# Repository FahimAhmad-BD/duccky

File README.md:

# Duccky v1.0

A production intent digital twin of a 28 cm, 15 DOF bipedal duck robot: parametric CAD, wiring, URDF and MJCF, reinforcement learning policies, and the robot runtime, all generated from one master design and built with free tools only.

Inspired by Pollen Robotics' Microduck. Duccky is a clean sheet design and contains no Microduck mechanical files.

## Status

| Phase | Scope | Status |
|---|---|---|
| 0 | Requirements, DOF, mass and power budgets | Done, [DCK-00](docs/00_requirements.md) |
| 1 | Sim first actuator sizing and servo selection | Done, [DCK-01](docs/01_actuator_sizing.md) |
| 2 | Electrical architecture, KiCad carrier board, harness | Done, [DCK-02](docs/02_electrical.md) |
| 3 | Mechanical CAD in Fusion with DFM rules | Next |
| 4 | Engineering validation: FEA, tolerance stacks, range of motion, power | Planned |
| 5 | Robot description: URDF, MJCF, ROS 2 package | Planned |
| 6 | RL training and sim to sim transfer | Planned |
| 7 | Software in the loop runtime | Planned |
| 8 | Manufacturing package: BOM, drawings, print and assembly guides | Planned |
| 9 | Portfolio site with browser simulation | Planned |

## Key decisions so far

| Decision | Choice |
|---|---|
| Actuation | 6 × ROBOTIS XC330-M288-T (hip pitch, knee, ankle), 9 × XL330-M288-T, knee assist spring 0.10 N m/rad |
| Mass | 825 g against an 850 g limit |
| Compute | Radxa ZERO 3W, 4 GB, 16 GB eMMC |
| Battery | Tool-free 2S cartridge, 2 × Molicel INR-18650-P28A, 20.6 Wh |
| Height | about 29.7 cm in nominal stance |
| Leg | 5 DOF, no ankle roll, thigh 52 mm, shank 46 mm |

## Repository layout

```
cad/          Fusion API scripts, STEP, STL, drawings
ecad/         KiCad project, BOM, harness definition
description/  generated URDF, MJCF, ROS 2 package
analysis/     sizing, FEA, tolerance stacks, power budget
training/     RL environments, configs, ONNX policies
runtime/      robot software, hardware abstraction layer, sim drivers
docs/         design record
web/          browser demo
```

## Toolchain

Fusion (personal use) · FreeCAD FEM and TechDraw · KiCad · MuJoCo · Blender · Python · GitHub Pages. All free.

## License

Code: Apache 2.0. Design files and documentation: CC BY 4.0. Third party assets keep their own licenses, listed in [docs/asset_register.md](docs/asset_register.md).

Author: Fahim Ahmad

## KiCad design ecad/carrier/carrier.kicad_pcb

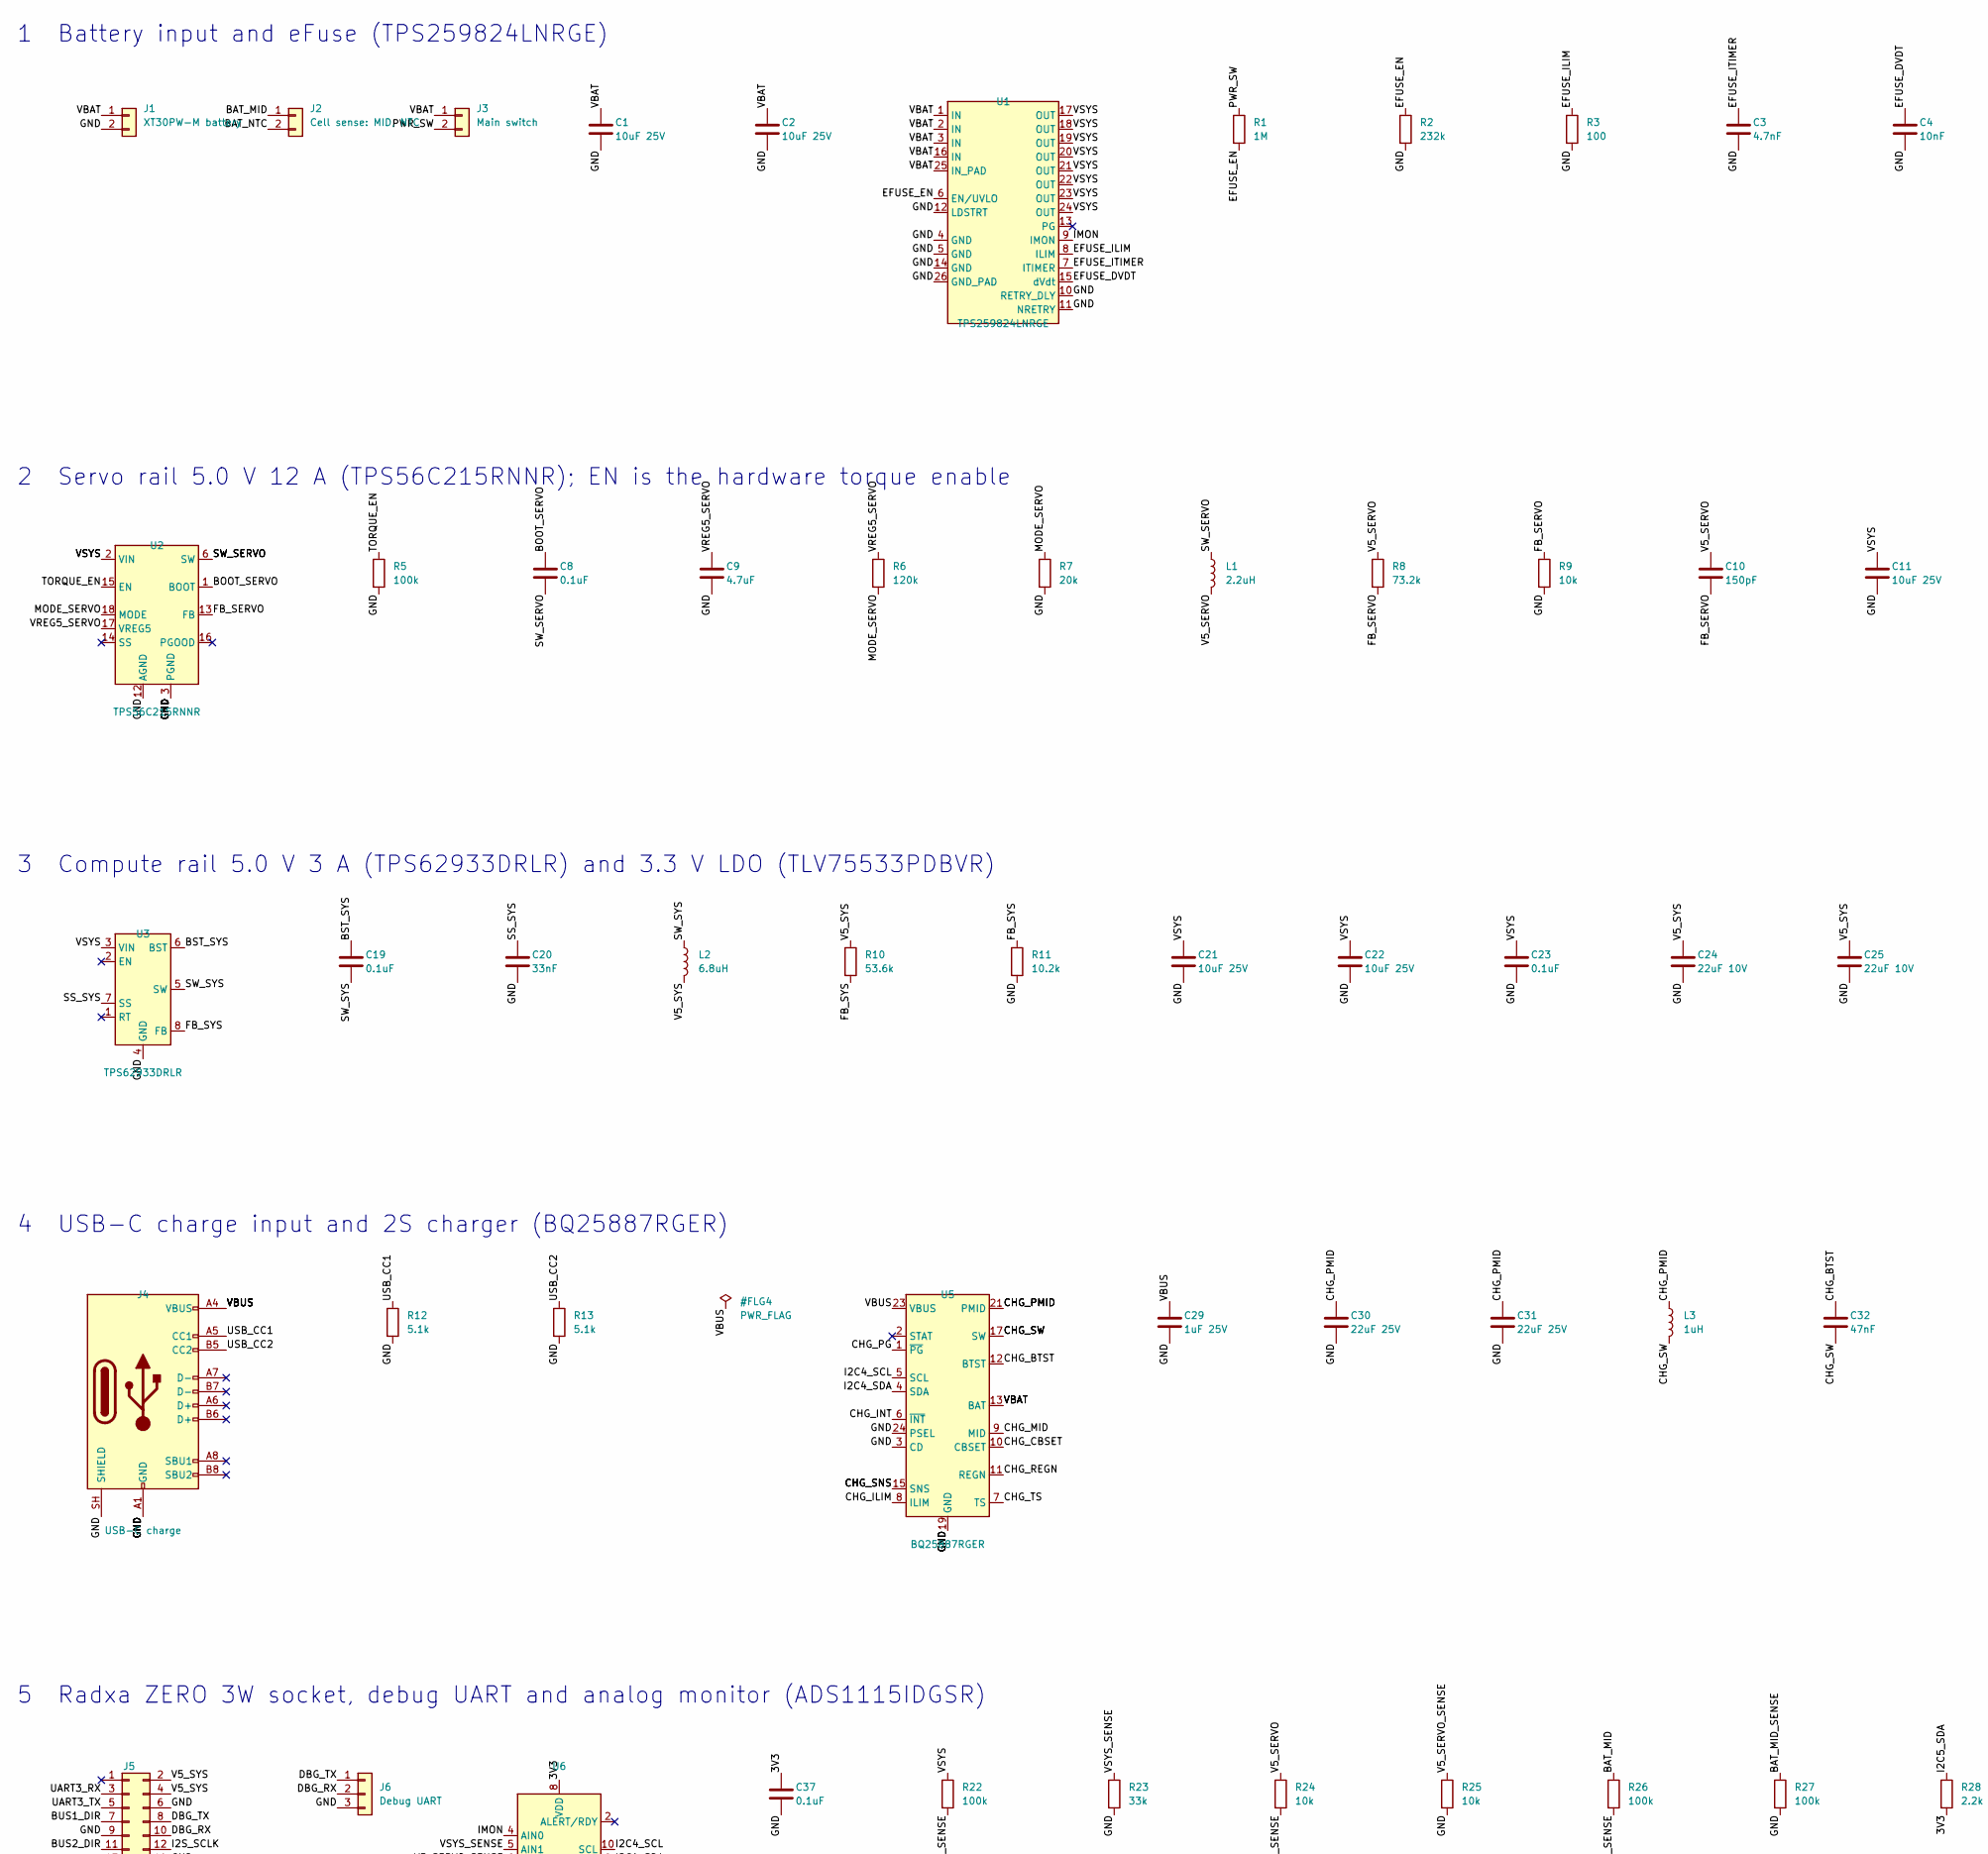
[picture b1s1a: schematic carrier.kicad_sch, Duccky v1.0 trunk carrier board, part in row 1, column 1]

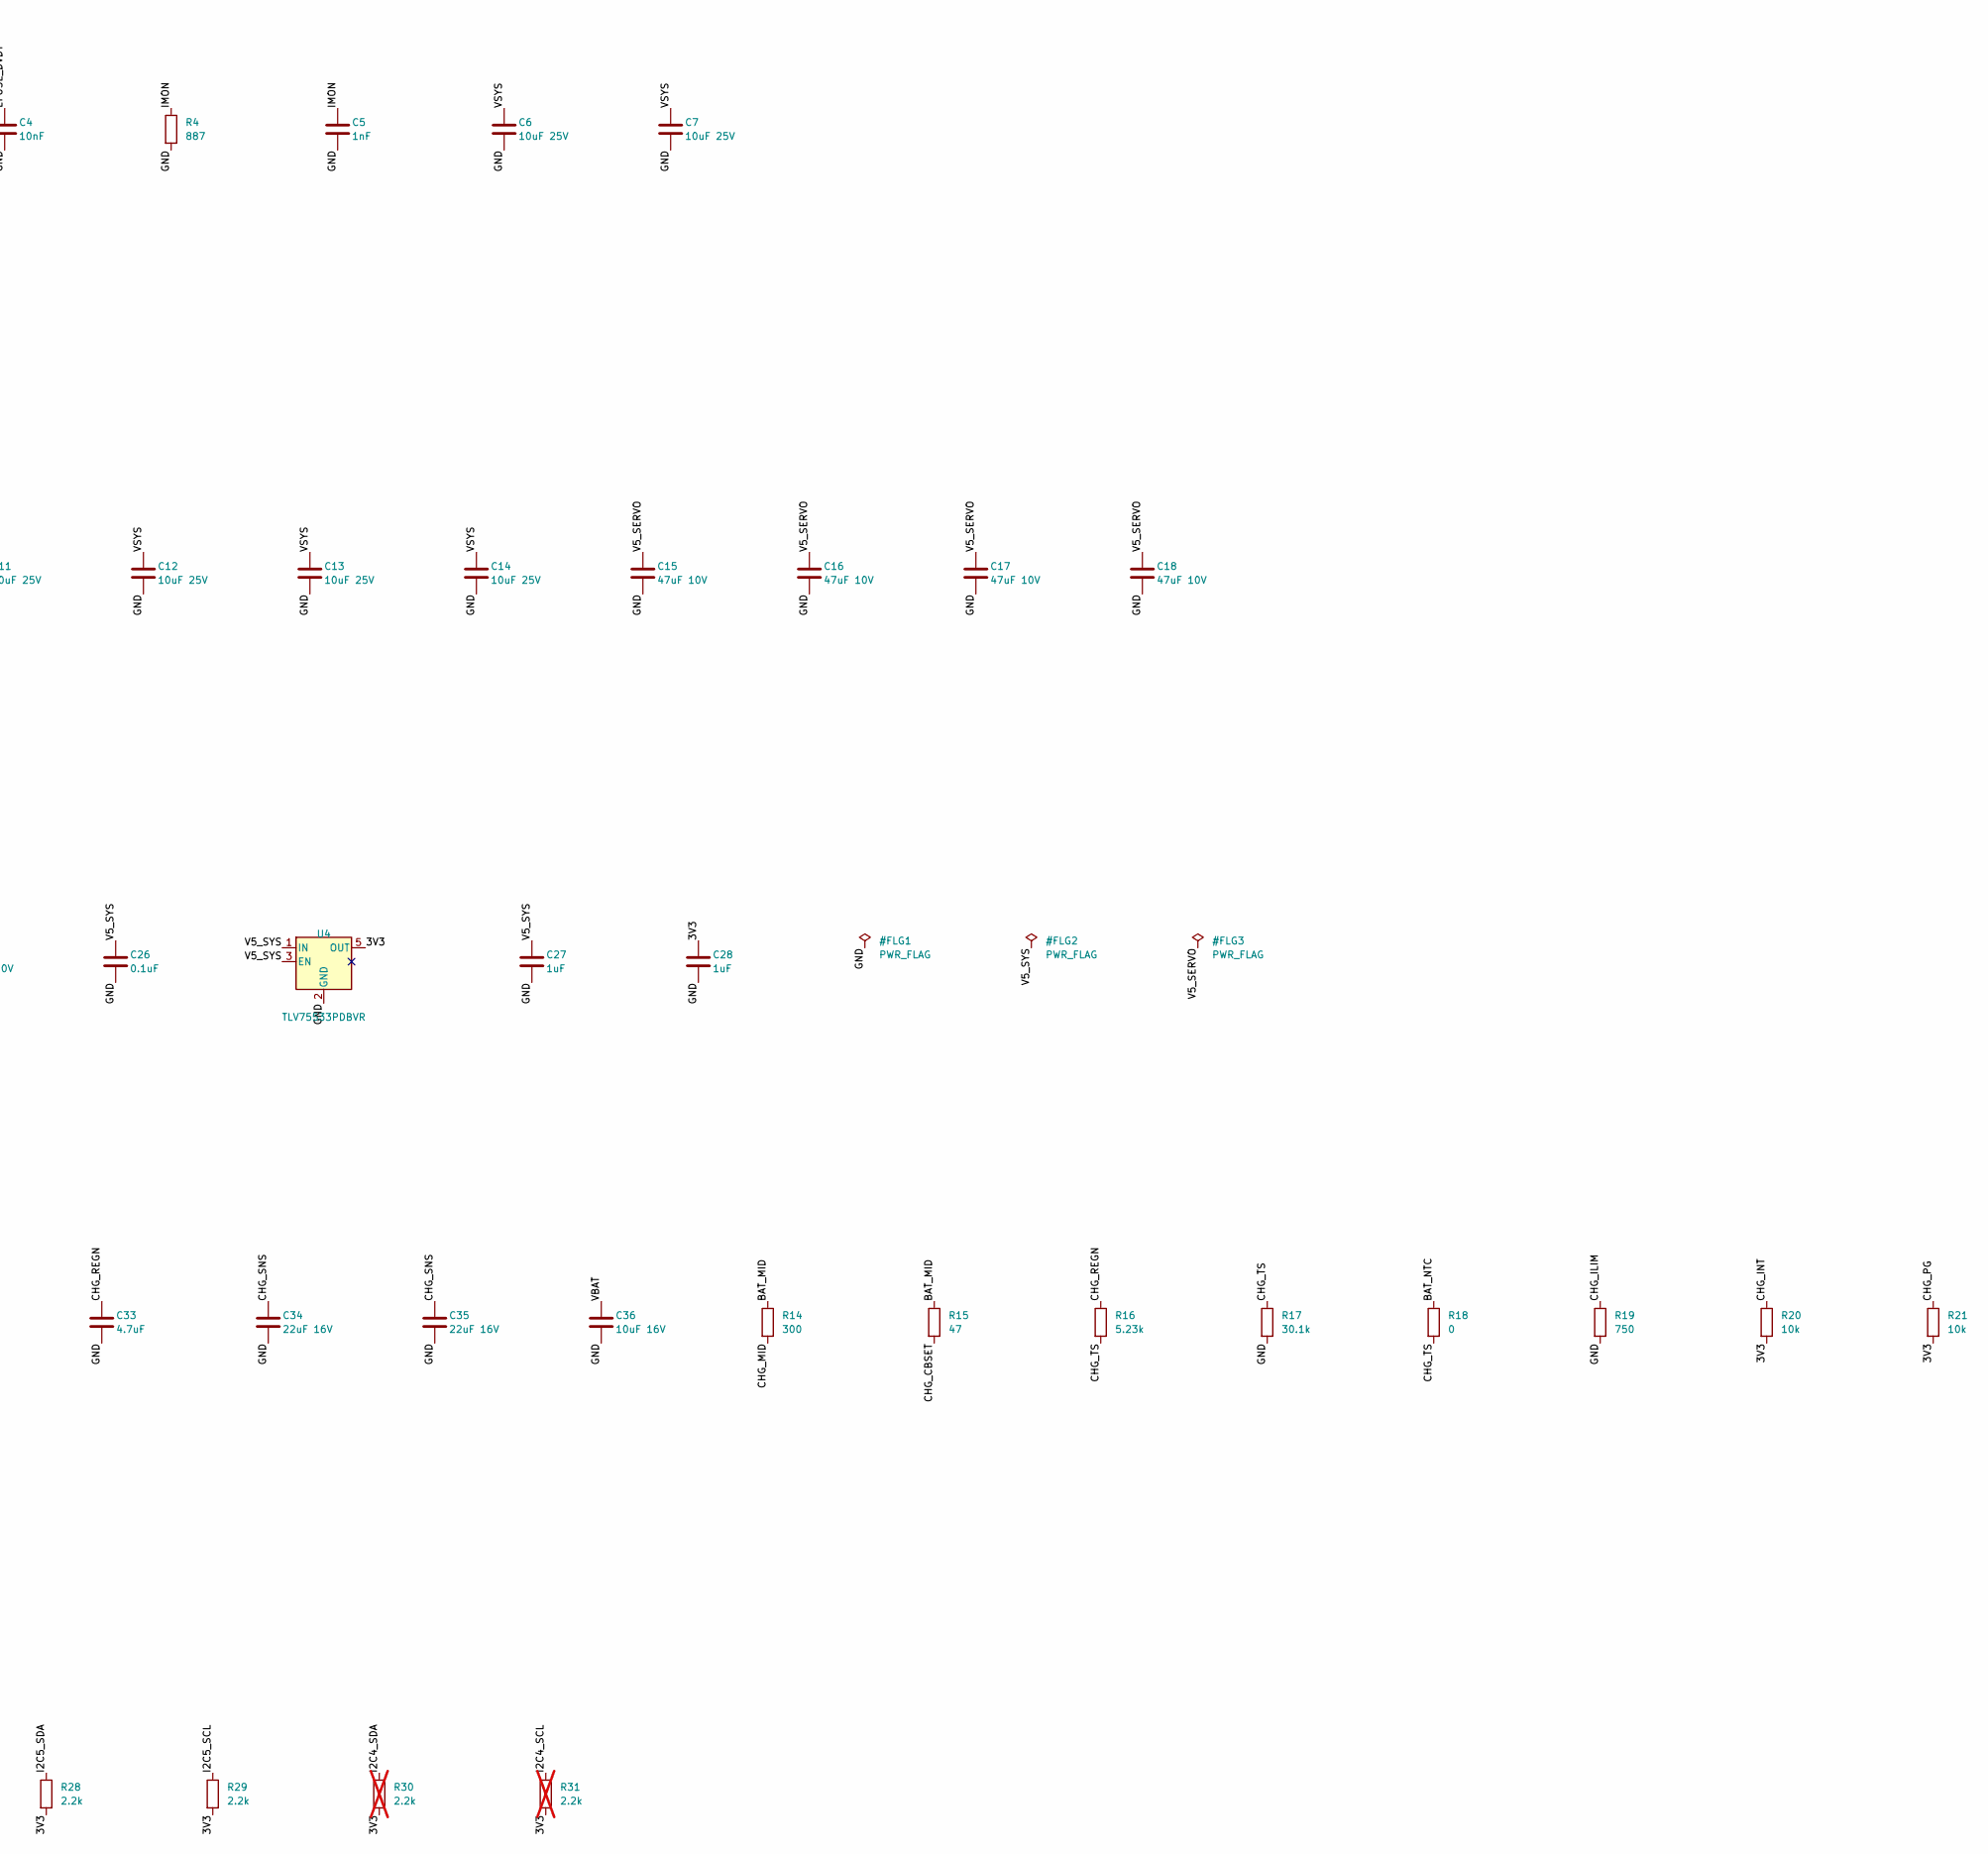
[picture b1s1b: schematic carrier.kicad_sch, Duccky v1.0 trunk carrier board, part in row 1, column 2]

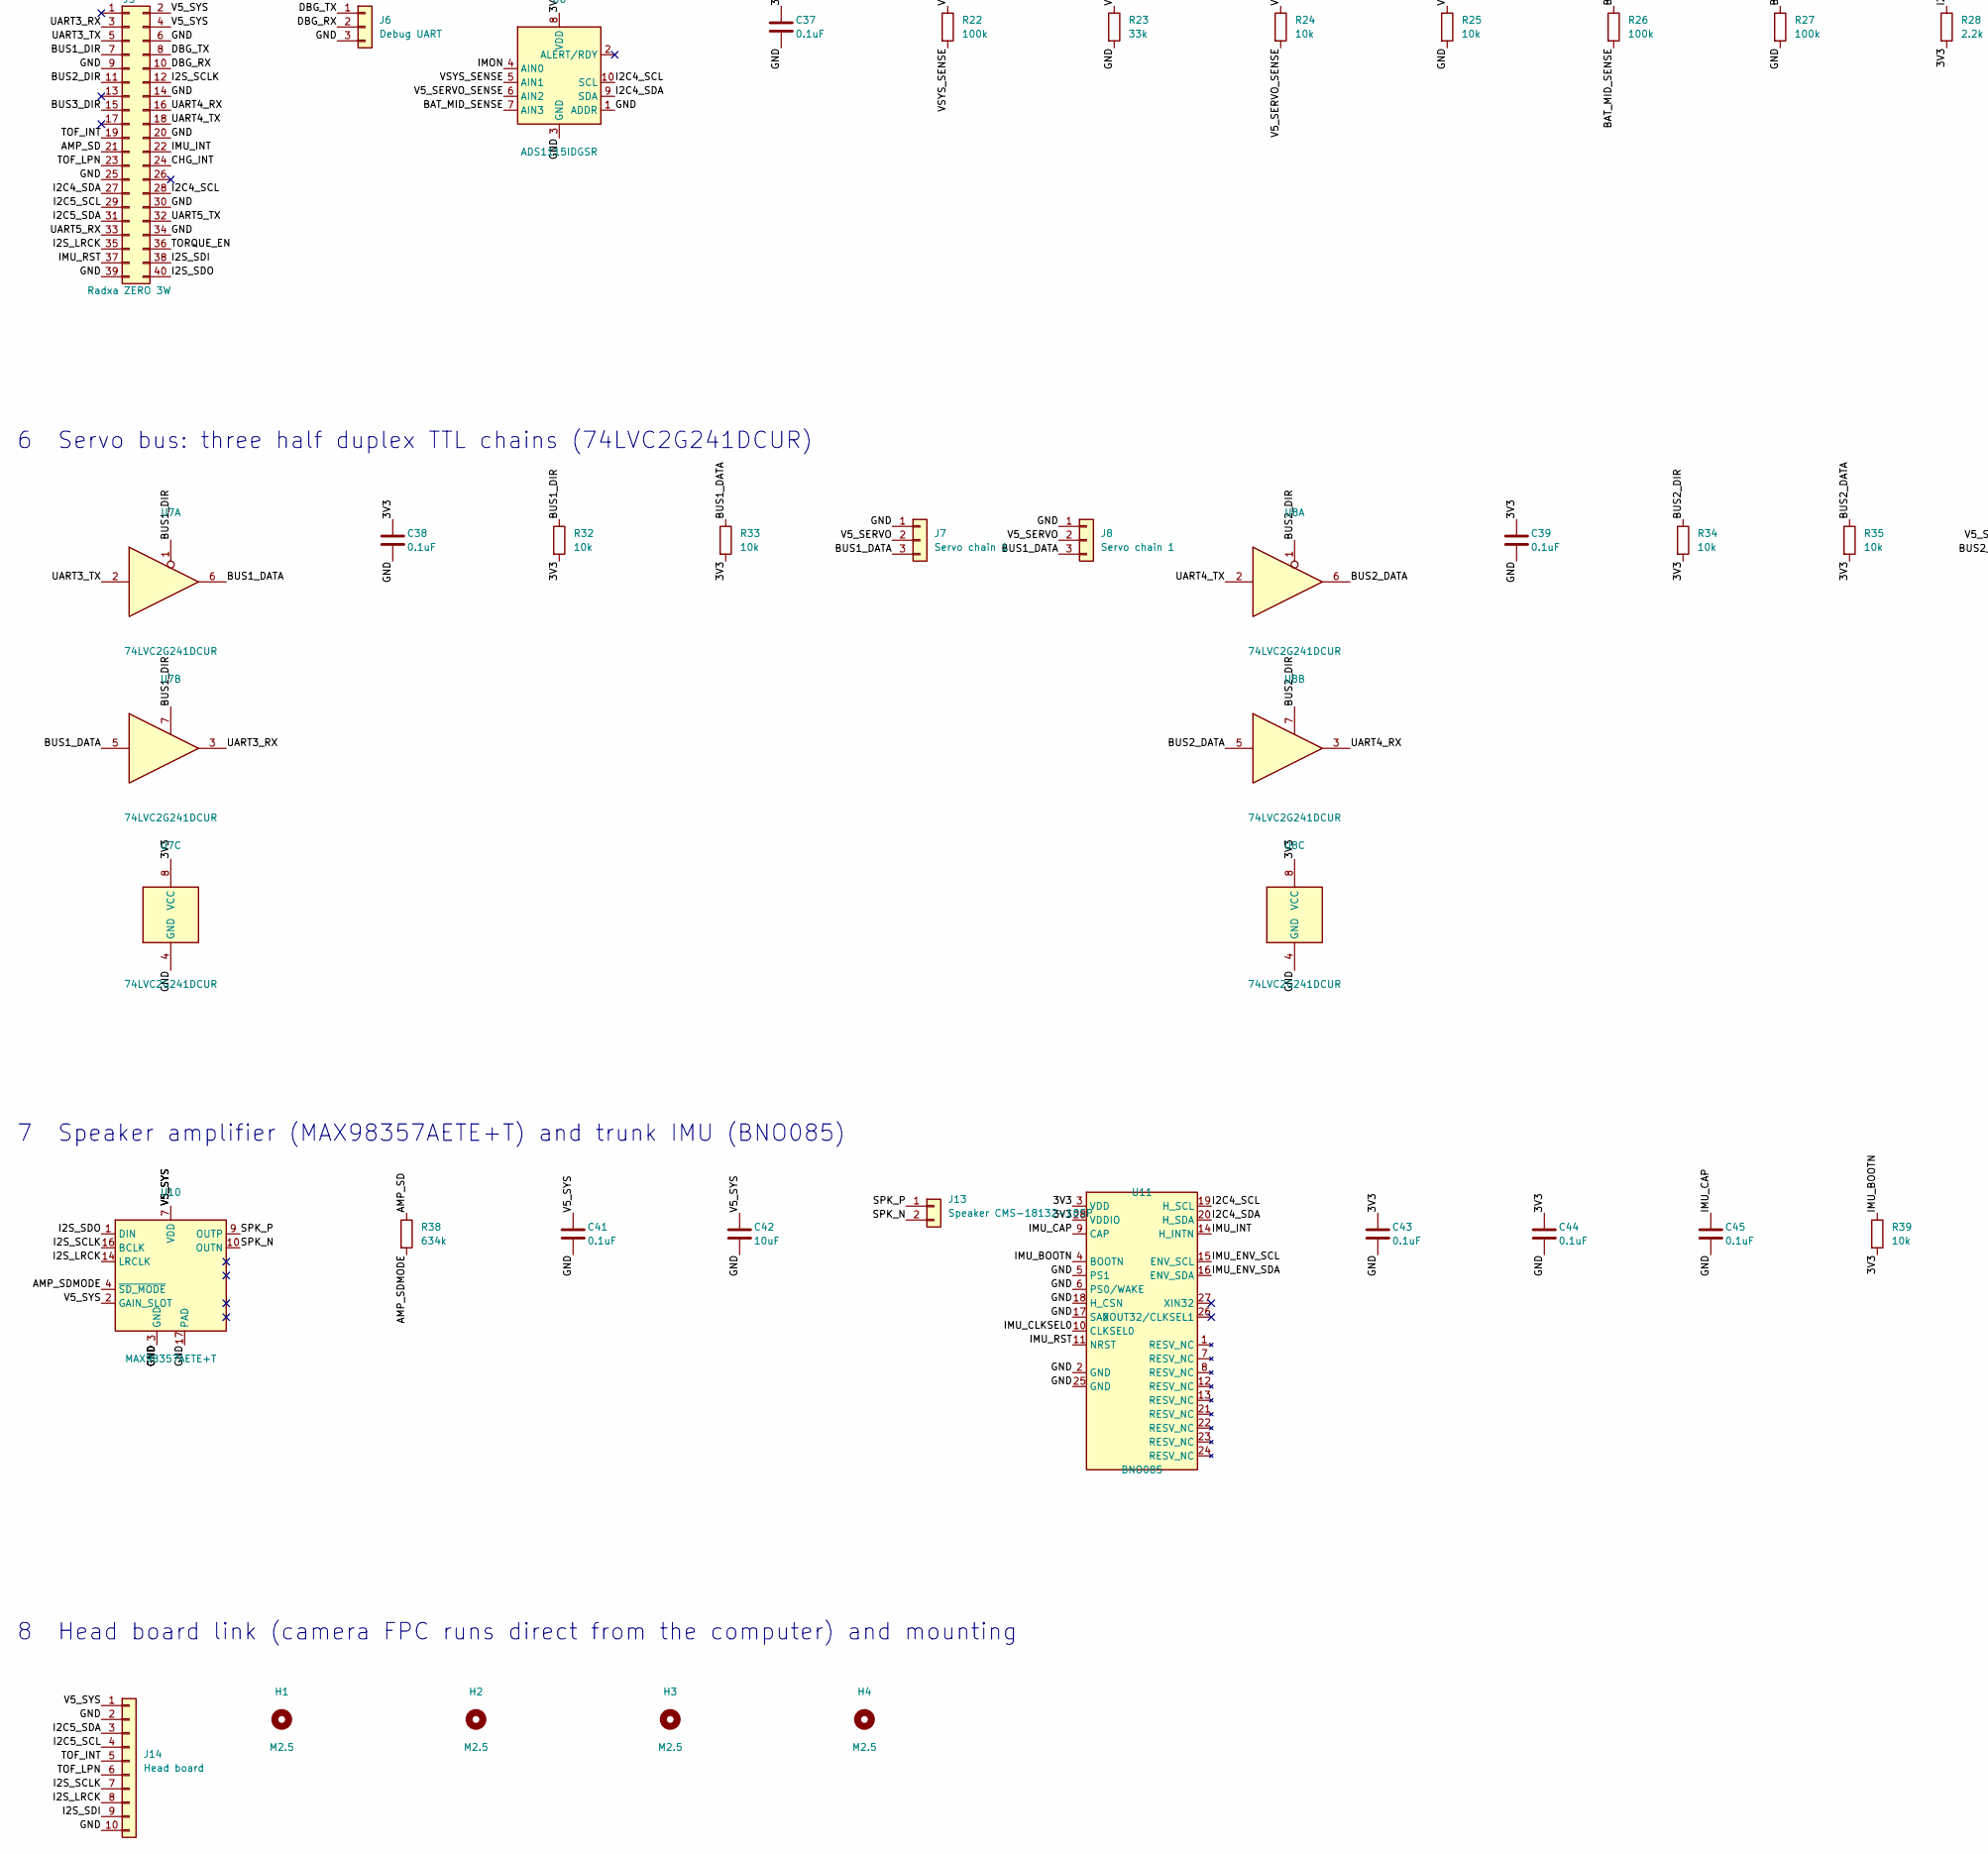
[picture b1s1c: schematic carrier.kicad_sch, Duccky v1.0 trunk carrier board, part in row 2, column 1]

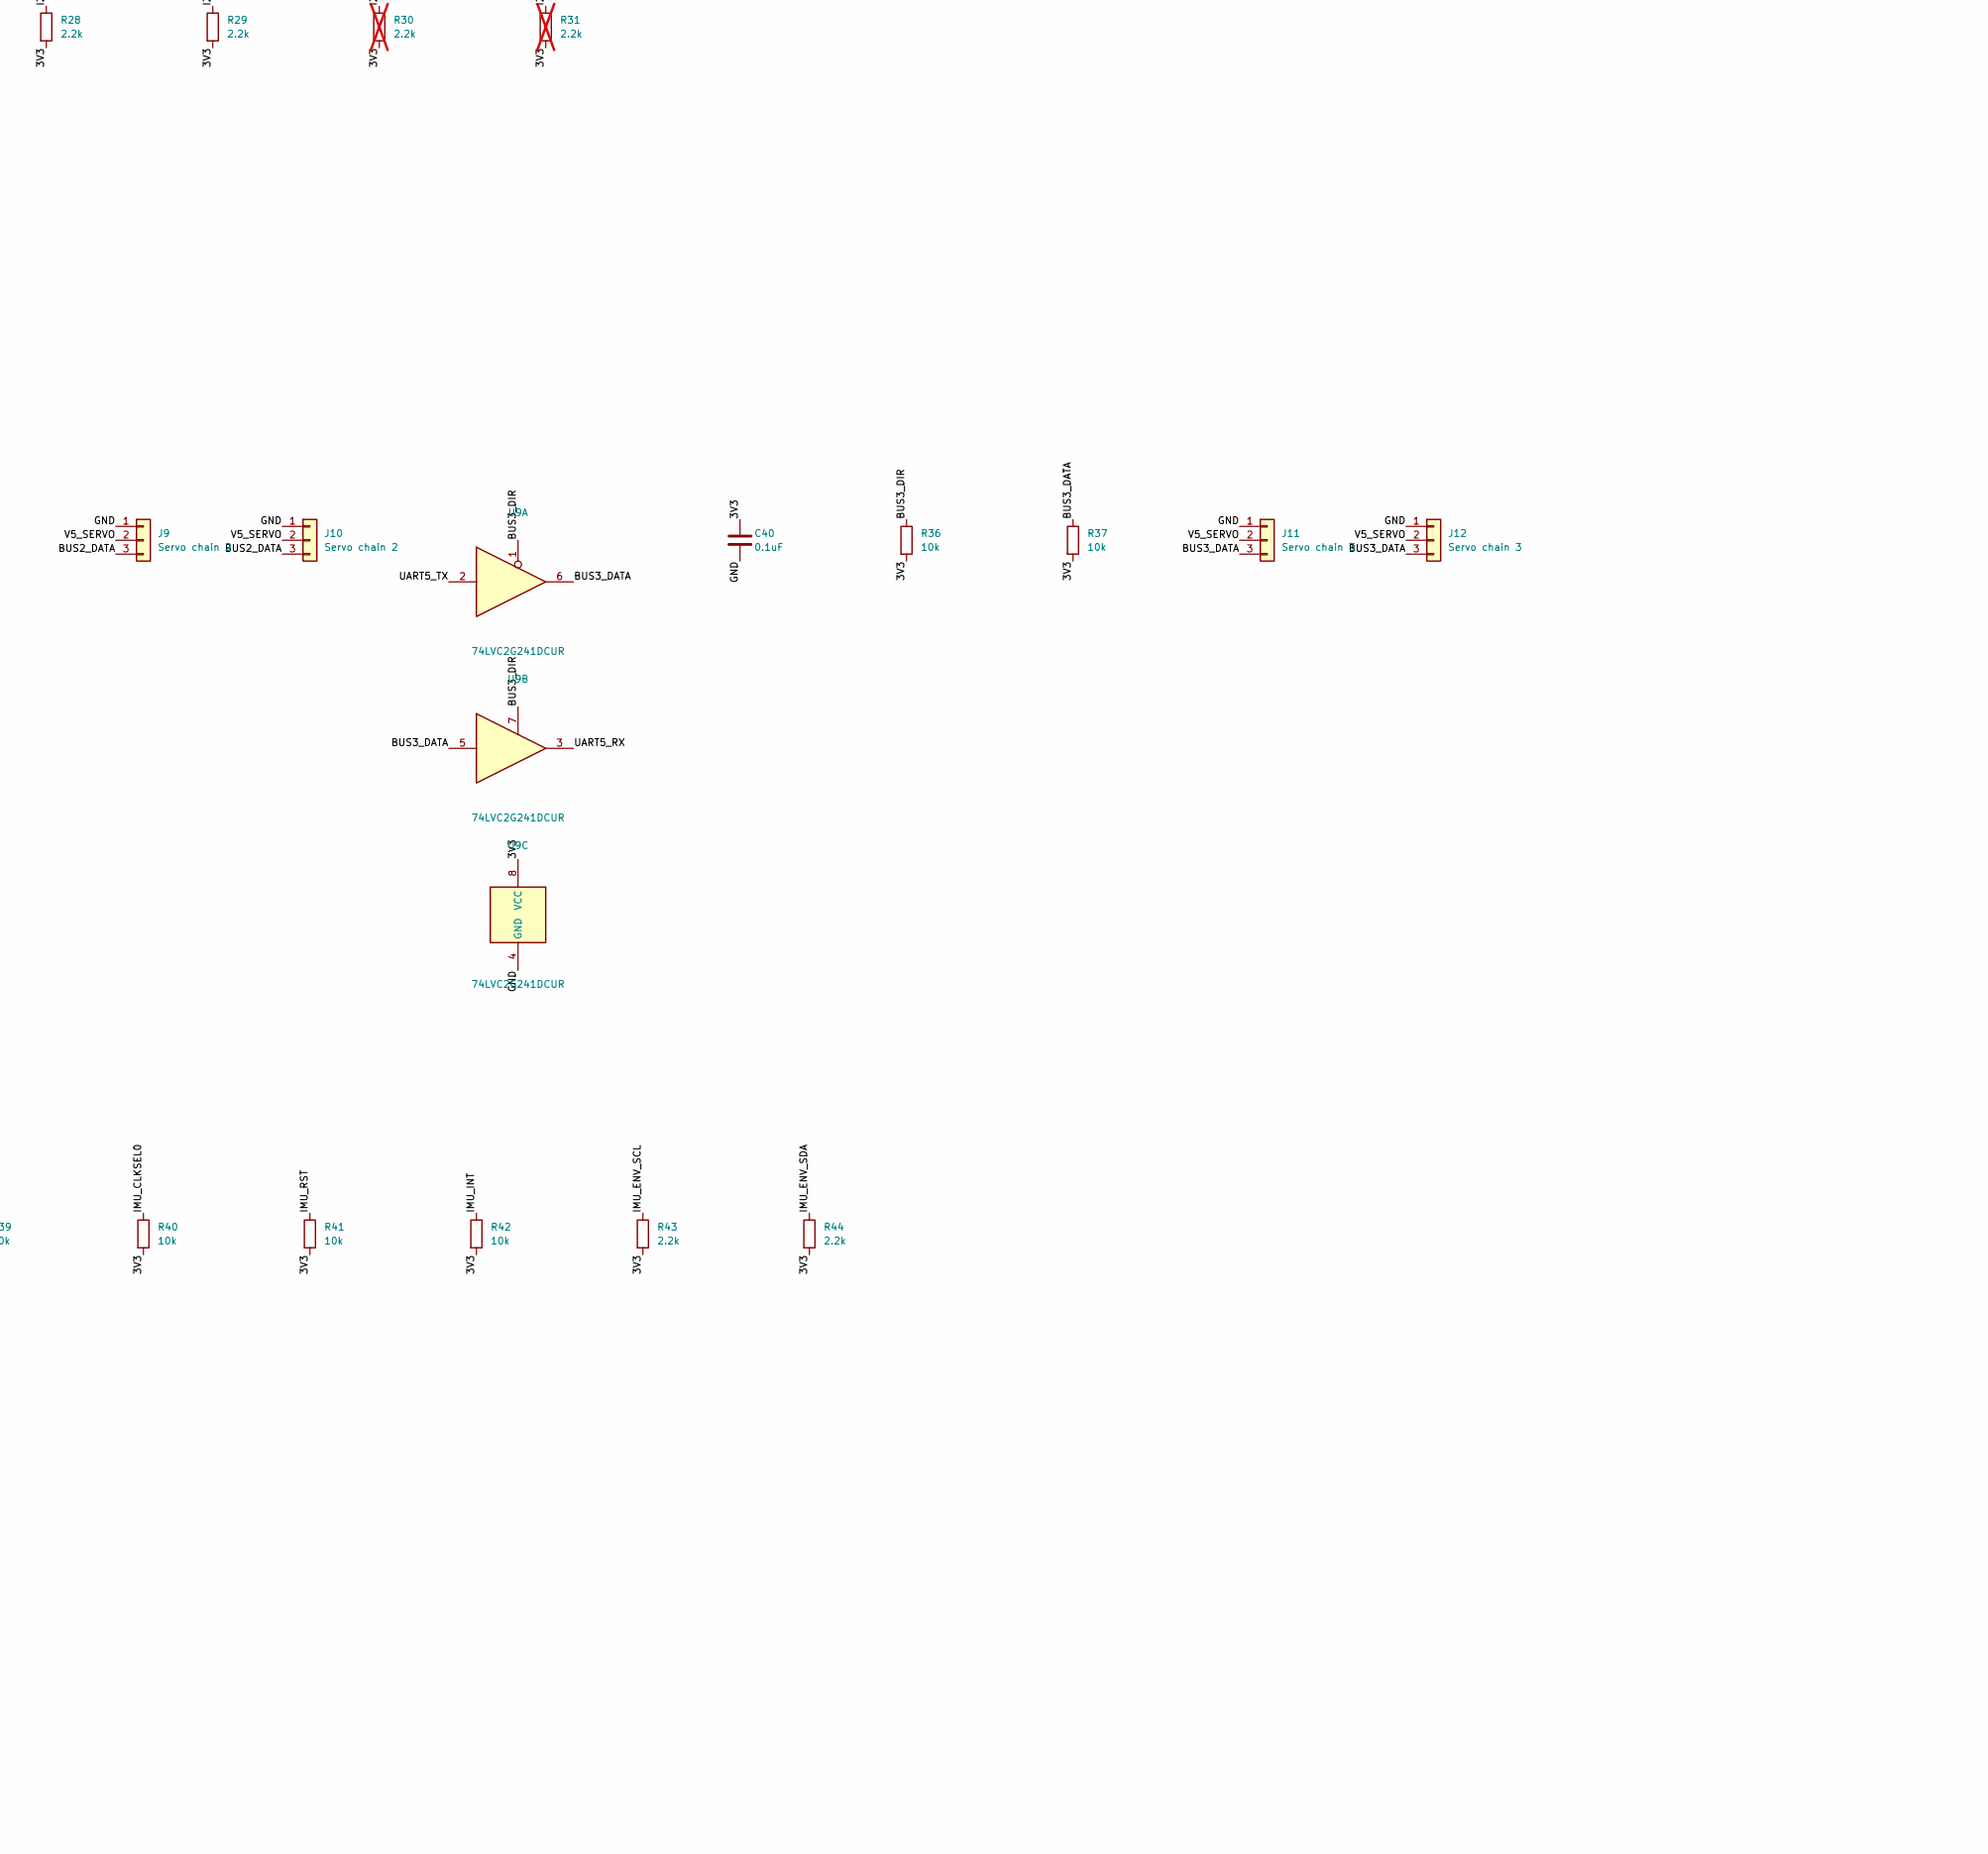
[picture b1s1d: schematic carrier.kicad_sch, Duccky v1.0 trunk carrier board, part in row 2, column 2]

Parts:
C1, C2, C6, C7, C11, C12, C13, C14, C21, C22: 10uF 25V; C_1206_3216Metric
C3: 4.7nF; C_0402_1005Metric
C4: 10nF; C_0402_1005Metric
C5: 1nF; C_0402_1005Metric
C8, C19, C23, C26, C37, C38, C39, C40, C41, C43, C44, C45: 0.1uF; C_0402_1005Metric
C9, C33: 4.7uF; C_0402_1005Metric
C10: 150pF; C_0402_1005Metric
C15, C16, C17, C18: 47uF 10V; C_1210_3225Metric
C20: 33nF; C_0402_1005Metric
C24, C25: 22uF 10V; C_1206_3216Metric
C27, C28: 1uF; C_0402_1005Metric
C29: 1uF 25V; C_0603_1608Metric
C30, C31: 22uF 25V; C_1206_3216Metric
C32: 47nF; C_0402_1005Metric
C34, C35: 22uF 16V; C_1206_3216Metric
C36: 10uF 16V; C_0805_2012Metric
C42: 10uF; C_0805_2012Metric
H1, H2, H3, H4: M2.5; MountingHole_2.7mm_M2.5
J1: XT30PW-M battery; AMASS_XT30PW-M_1x02_P2.50mm_Horizontal; MPN Amass XT30PW-M
J2: Cell sense: MID, NTC; JST_GH_SM02B-GHS-TB_1x02-1MP_P1.25mm_Horizontal; MPN JST SM02B-GHS-TB
J3: Main switch; JST_GH_SM02B-GHS-TB_1x02-1MP_P1.25mm_Horizontal; MPN JST SM02B-GHS-TB
J4: USB-C charge; USB_C_Receptacle_GCT_USB4105-xx-A_16P_TopMnt_Horizontal; MPN GCT USB4105-GF-A
J5: Radxa ZERO 3W; PinSocket_2x20_P2.54mm_Vertical
J6: Debug UART; JST_SH_SM03B-SRSS-TB_1x03-1MP_P1.00mm_Horizontal; MPN JST SM03B-SRSS-TB
J7, J8: Servo chain 1; JST_EH_B3B-EH-A_1x03_P2.50mm_Vertical; MPN JST B3B-EH-A
J9, J10: Servo chain 2; JST_EH_B3B-EH-A_1x03_P2.50mm_Vertical; MPN JST B3B-EH-A
J11, J12: Servo chain 3; JST_EH_B3B-EH-A_1x03_P2.50mm_Vertical; MPN JST B3B-EH-A
J13: Speaker CMS-18132-18SP; JST_GH_SM02B-GHS-TB_1x02-1MP_P1.25mm_Horizontal; MPN JST SM02B-GHS-TB
J14: Head board; JST_GH_SM10B-GHS-TB_1x10-1MP_P1.25mm_Horizontal; MPN JST SM10B-GHS-TB
L1: 2.2uH; L_Coilcraft_XAL7030-222; MPN Coilcraft XAL7030-222
L2: 6.8uH; L_Coilcraft_XAL5030-XXX; MPN 6.8 uH, Isat >= 5.8 A
L3: 1uH; L_1008_2520Metric; MPN Murata DFE252012F-1R0M
R1: 1M; R_0402_1005Metric
R2: 232k; R_0402_1005Metric
R3: 100; R_0402_1005Metric
R4: 887; R_0402_1005Metric
R5, R22, R26, R27: 100k; R_0402_1005Metric
R6: 120k; R_0402_1005Metric
R7: 20k; R_0402_1005Metric
R8: 73.2k; R_0402_1005Metric
R9, R20, R21, R24, R25, R32, R33, R34, R35, R36, R37, R39, R40, R41, R42: 10k; R_0402_1005Metric
R10: 53.6k; R_0402_1005Metric
R11: 10.2k; R_0402_1005Metric
R12, R13: 5.1k; R_0402_1005Metric
R14: 300; R_0402_1005Metric
R15: 47; R_2010_5025Metric
R16: 5.23k; R_0402_1005Metric
R17: 30.1k; R_0402_1005Metric
R18: 0; R_0402_1005Metric
R19: 750; R_0402_1005Metric
R23: 33k; R_0402_1005Metric
R28, R29, R43, R44: 2.2k; R_0402_1005Metric
R30, R31: 2.2k; R_0402_1005Metric; not fitted
R38: 634k; R_0402_1005Metric
U1: TPS259824LNRGE; Texas_RGE0024M_TPS25982
U2: TPS56C215RNNR; Texas_RNN0018A; MPN TPS56C215RNNR
U3: TPS62933DRLR; SOT-583-8; MPN TPS62933DRLR
U4: TLV75533PDBVR; SOT-23-5; MPN TLV75533PDBVR
U5: BQ25887RGER; Texas_RGE0024H_VQFN-24-1EP_4x4mm_P0.5mm_EP2.7x2.7mm; MPN BQ25887RGER
U6: ADS1115IDGSR; TSSOP-10_3x3mm_P0.5mm; MPN ADS1115IDGSR
U7, U8, U9: 74LVC2G241DCUR; VSSOP-8_2.3x2mm_P0.5mm; MPN SN74LVC2G241DCUR
U10: MAX98357AETE+T; TQFN-16-1EP_3x3mm_P0.5mm_EP1.23x1.23mm; MPN MAX98357AETE+T
U11: BNO085; LGA-28_5.2x3.8mm_P0.5mm; MPN BNO085

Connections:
/3V3: C28.1, C37.1, C38.1, C39.1, C40.1, C43.1, C44.1, R20.2, R21.2, R28.2, R29.2, R30.2, R31.2, R32.2, R33.2, R34.2, R35.2, R36.2, R37.2, R39.2, R40.2, R41.2, R42.2, R43.2, R44.2, U4.5 (OUT), U6.8 (VDD), U7.8 (VCC), U8.8 (VCC), U9.8 (VCC), U11.3 (VDD), U11.28 (VDDIO)
/AMP_SD: J5.21, R38.1
/AMP_SDMODE: R38.2, U10.4 (~SD_MODE)
/BAT_MID: J2.1, R14.1, R15.1, R26.1
/BAT_MID_SENSE: R26.2, R27.1, U6.7 (AIN3)
/BAT_NTC: J2.2, R18.1
/BOOT_SERVO: C8.1, U2.1 (BOOT)
/BST_SYS: C19.1, U3.6 (BST)
/BUS1_DATA: J7.3, J8.3, R33.1, U7.5, U7.6
/BUS1_DIR: J5.7, R32.1, U7.1, U7.7
/BUS2_DATA: J9.3, J10.3, R35.1, U8.5, U8.6
/BUS2_DIR: J5.11, R34.1, U8.1, U8.7
/BUS3_DATA: J11.3, J12.3, R37.1, U9.5, U9.6
/BUS3_DIR: J5.15, R36.1, U9.1, U9.7
/CHG_BTST: C32.1, U5.12 (BTST)
/CHG_CBSET: R15.2, U5.10 (CBSET)
/CHG_ILIM: R19.1, U5.8 (ILIM)
/CHG_INT: J5.24, R20.1, U5.6 (~INT)
/CHG_MID: R14.2, U5.9 (MID)
/CHG_PG: R21.1, U5.1 (~PG)
/CHG_PMID: C30.1, C31.1, L3.1, U5.21 (PMID), U5.22 (PMID)
/CHG_REGN: C33.1, R16.1, U5.11 (REGN)
/CHG_SNS: C34.1, C35.1, U5.15 (SNS), U5.16 (SNS)
/CHG_SW: C32.2, L3.2, U5.17 (SW), U5.18 (SW)
/CHG_TS: R16.2, R17.1, R18.2, U5.7 (TS)
/DBG_RX: J5.10, J6.2
/DBG_TX: J5.8, J6.1
/EFUSE_DVDT: C4.1, U1.15 (dVdt)
/EFUSE_EN: R1.2, R2.1, U1.6 (EN/UVLO)
/EFUSE_ILIM: R3.1, U1.8 (ILIM)
/EFUSE_ITIMER: C3.1, U1.7 (ITIMER)
/FB_SERVO: C10.2, R8.2, R9.1, U2.13 (FB)
/FB_SYS: R10.2, R11.1, U3.8 (FB)
/GND: C1.2, C2.2, C3.2, C4.2, C5.2, C6.2, C7.2, C9.2, C11.2, C12.2, C13.2, C14.2, C15.2, C16.2, C17.2, C18.2, C20.2, C21.2, C22.2, C23.2, C24.2, C25.2, C26.2, C27.2, C28.2, C29.2, C30.2, C31.2, C33.2, C34.2, C35.2, C36.2, C37.2, C38.2, C39.2, C40.2, C41.2, C42.2, C43.2, C44.2, C45.2, J1.2, J4.A1 (GND), J4.A12 (GND), J4.B1 (GND), J4.B12 (GND), J4.SH (SHIELD), J5.6, J5.9, J5.14, J5.20, J5.25, J5.30, J5.34, J5.39, J6.3, J7.1, J8.1, J9.1, J10.1, J11.1, J12.1, J14.2, J14.10, R2.2, R3.2, R4.2, R5.2, R7.2, R9.2, R11.2, R12.2, R13.2, R17.2, R19.2, R23.2, R25.2, R27.2, U1.4 (GND), U1.5 (GND), U1.10 (RETRY_DLY), U1.11 (NRETRY), U1.12 (LDSTRT), U1.14 (GND), U1.26 (GND_PAD), U2.3 (PGND), U2.4 (PGND), U2.5 (PGND), U2.8 (PGND), U2.9 (PGND), U2.10 (PGND), U2.12 (AGND), U3.4 (GND), U4.2 (GND), U5.3 (CD), U5.19 (GND), U5.20 (GND), U5.24 (PSEL), U5.25 (GND), U6.1 (ADDR), U6.3 (GND), U7.4 (GND), U8.4 (GND), U9.4 (GND), U10.3 (GND), U10.11 (GND), U10.15 (GND), U10.17 (PAD), U11.2 (GND), U11.5 (PS1), U11.6 (PS0/WAKE), U11.17 (SA0), U11.18 (H_CSN), U11.25 (GND)
/I2C4_SCL: J5.28, R31.1, U5.5 (SCL), U6.10 (SCL), U11.19 (H_SCL)
/I2C4_SDA: J5.27, R30.1, U5.4 (SDA), U6.9 (SDA), U11.20 (H_SDA)
/I2C5_SCL: J5.29, J14.4, R29.1
/I2C5_SDA: J5.31, J14.3, R28.1
/I2S_LRCK: J5.35, J14.8, U10.14 (LRCLK)
/I2S_SCLK: J5.12, J14.7, U10.16 (BCLK)
/I2S_SDI: J5.38, J14.9
/I2S_SDO: J5.40, U10.1 (DIN)
/IMON: C5.1, R4.1, U1.9 (IMON), U6.4 (AIN0)
/IMU_BOOTN: R39.1, U11.4 (BOOTN)
/IMU_CAP: C45.1, U11.9 (CAP)
/IMU_CLKSEL0: R40.1, U11.10 (CLKSEL0)
/IMU_ENV_SCL: R43.1, U11.15 (ENV_SCL)
/IMU_ENV_SDA: R44.1, U11.16 (ENV_SDA)
/IMU_INT: J5.22, R42.1, U11.14 (H_INTN)
/IMU_RST: J5.37, R41.1, U11.11 (NRST)
/MODE_SERVO: R6.2, R7.1, U2.18 (MODE)
/PWR_SW: J3.2, R1.1
/SPK_N: J13.2, U10.10 (OUTN)
/SPK_P: J13.1, U10.9 (OUTP)
/SS_SYS: C20.1, U3.7 (SS)
/SW_SERVO: C8.2, L1.1, U2.6 (SW), U2.7 (SW)
/SW_SYS: C19.2, L2.1, U3.5 (SW)
/TOF_INT: J5.19, J14.5
/TOF_LPN: J5.23, J14.6
/TORQUE_EN: J5.36, R5.1, U2.15 (EN)
/UART3_RX: J5.3, U7.3
/UART3_TX: J5.5, U7.2
/UART4_RX: J5.16, U8.3
/UART4_TX: J5.18, U8.2
/UART5_RX: J5.33, U9.3
/UART5_TX: J5.32, U9.2
/USB_CC1: J4.A5 (CC1), R12.1
/USB_CC2: J4.B5 (CC2), R13.1
/V5_SERVO: C10.1, C15.1, C16.1, C17.1, C18.1, J7.2, J8.2, J9.2, J10.2, J11.2, J12.2, L1.2, R8.1, R24.1
/V5_SERVO_SENSE: R24.2, R25.1, U6.6 (AIN2)
/V5_SYS: C24.1, C25.1, C26.1, C27.1, C41.1, C42.1, J5.2, J5.4, J14.1, L2.2, R10.1, U4.1 (IN), U4.3 (EN), U10.2 (GAIN_SLOT), U10.7 (VDD), U10.8 (VDD)
/VBAT: C1.1, C2.1, C36.1, J1.1, J3.1, U1.1 (IN), U1.2 (IN), U1.3 (IN), U1.16 (IN), U1.25 (IN_PAD), U5.13 (BAT), U5.14 (BAT)
/VBUS: C29.1, J4.A4 (VBUS), J4.A9 (VBUS), J4.B4 (VBUS), J4.B9 (VBUS), U5.23 (VBUS)
/VREG5_SERVO: C9.1, R6.1, U2.17 (VREG5)
/VSYS: C6.1, C7.1, C11.1, C12.1, C13.1, C14.1, C21.1, C22.1, C23.1, R22.1, U1.17 (OUT), U1.18 (OUT), U1.19 (OUT), U1.20 (OUT), U1.21 (OUT), U1.22 (OUT), U1.23 (OUT), U1.24 (OUT), U2.2 (VIN), U2.11 (VIN), U3.3 (VIN)
/VSYS_SENSE: R22.2, R23.1, U6.5 (AIN1)

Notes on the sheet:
1 Battery input and eFuse (TPS259824LNRGE)
2 Servo rail 5.0 V 12 A (TPS56C215RNNR); EN is the hardware torque enable
3 Compute rail 5.0 V 3 A (TPS62933DRLR) and 3.3 V LDO (TLV75533PDBVR)
4 USB-C charge input and 2S charger (BQ25887RGER)
5 Radxa ZERO 3W socket, debug UART and analog monitor (ADS1115IDGSR)
6 Servo bus: three half duplex TTL chains (74LVC2G241DCUR)
7 Speaker amplifier (MAX98357AETE+T) and trunk IMU (BNO085)
8 Head board link (camera FPC runs direct from the computer) and mounting

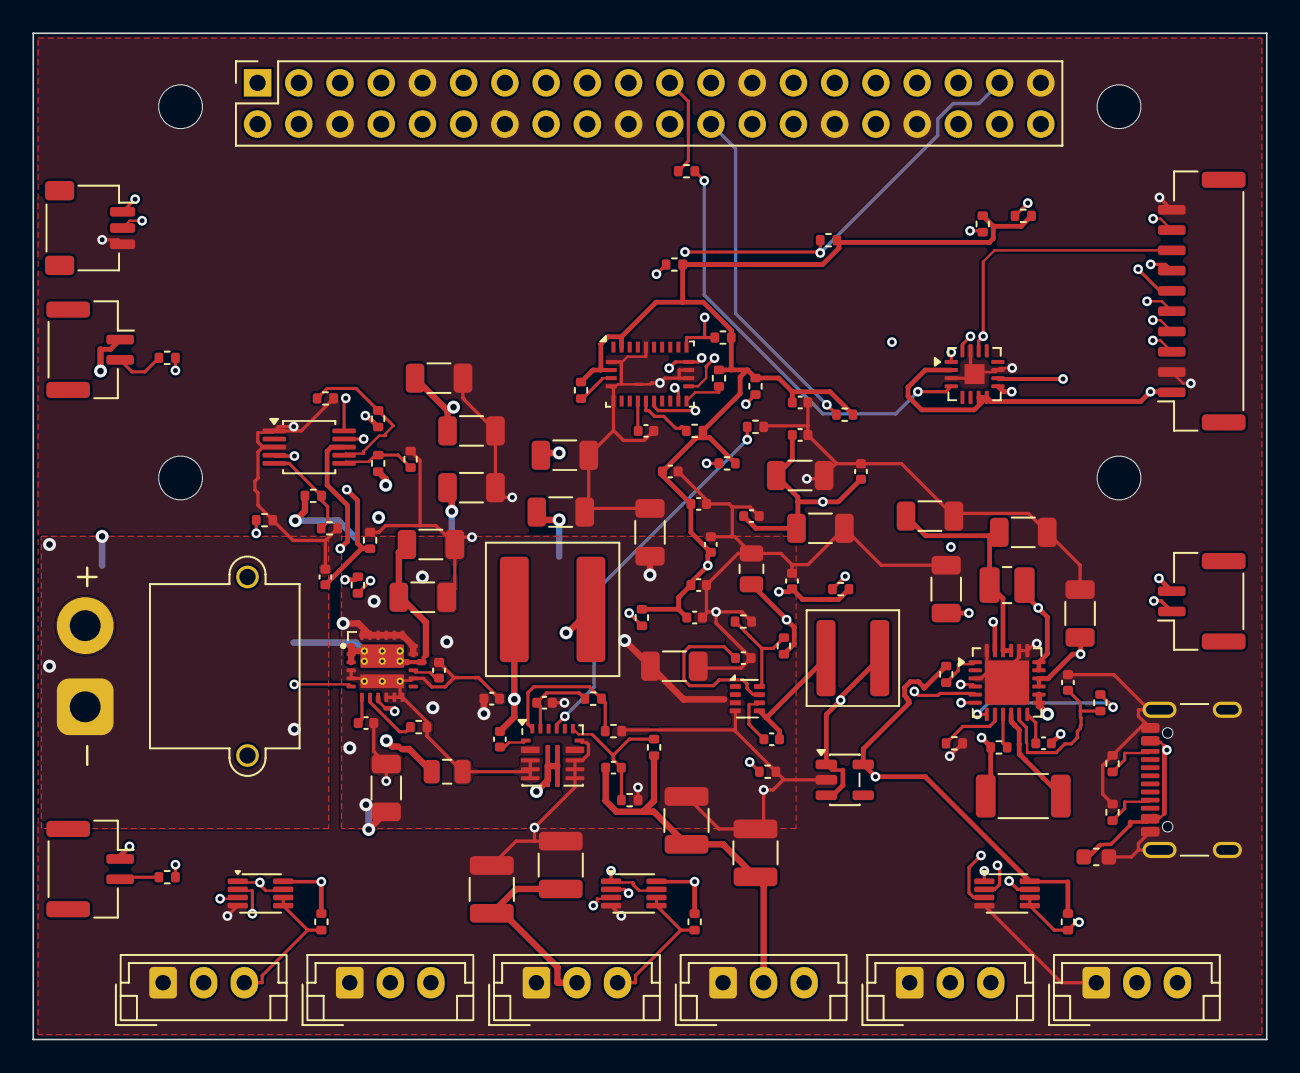
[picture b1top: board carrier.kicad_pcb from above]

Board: 4 copper layers, 76.0 x 62.0 mm, 121 parts (0 on the bottom side), 76 nets.
